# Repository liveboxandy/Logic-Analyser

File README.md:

# Logic-Analyser
Cloned and modified from  (https://github.com/gusmanb/logicanalyzer)

Changes from the above are,

1 - Pico can be mounted on headers. Suggest Samtec BBL or SL style.
2 - Uses 0805 rather than 0402 SMT components so I can see and solder them.
3 - Has keepout area for Pico WiFi.
4 - PCB is slightly larger than the orignal.
5 - No ther changes that I can remember

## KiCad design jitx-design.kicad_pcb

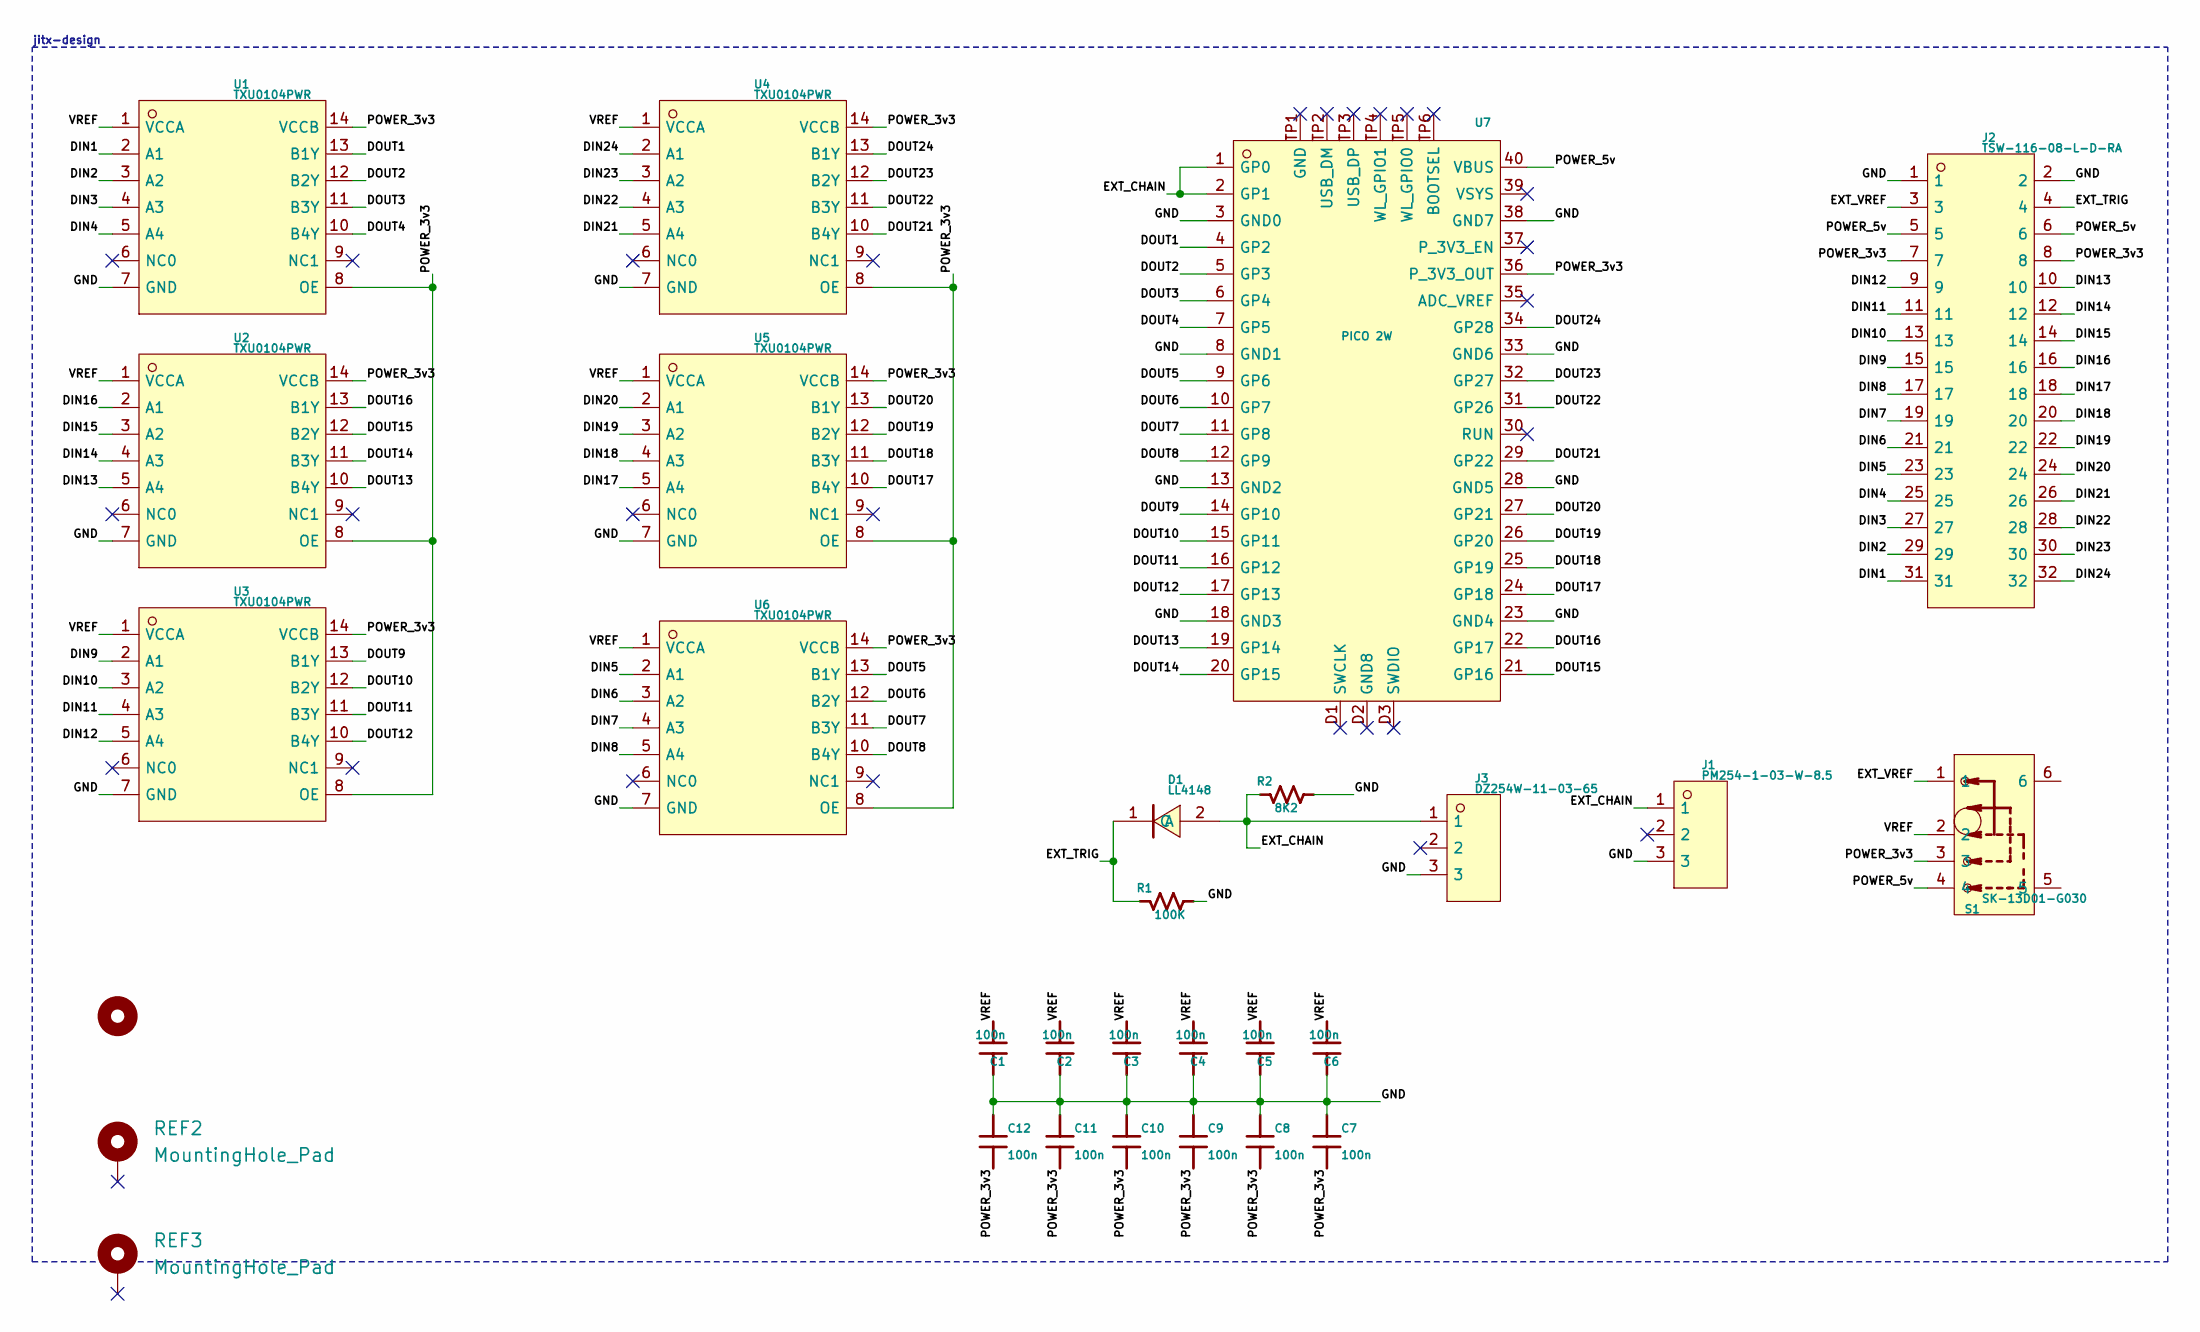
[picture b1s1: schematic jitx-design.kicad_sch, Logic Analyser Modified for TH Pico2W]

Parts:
C1, C2, C3, C4, C5, C6, C7, C8, C9, C10, C11, C12: 100n; C_0805_2012Metric_Pad1.18x1.45mm_HandSolder; MPN 0402X104M160CT
D1: LL4148; LL_34_L3_5_W1_5_RD; MPN LL4148
J1: PM254-1-03-W-8.5; HDR_TH_3P_P2_54_H_F_W10_0_N; MPN PM254-1-03-W-8.5
J2: TSW-116-08-L-D-RA; HDRRA32W64P254_2X16_4064X254X610P
J3: DZ254W-11-03-65; HDR_TH_3P_P2_54_H_M_W10_0; MPN DZ254W-11-03-65
R1: 100K; R_0805_2012Metric_Pad1.20x1.40mm_HandSolder; MPN CRCW0402100KFKEE
R2: 8K2; R_0805_2012Metric_Pad1.20x1.40mm_HandSolder; MPN CR0402AJW-822GLF
REF1: MountingHole_Pad; MountingHole_2.7mm_M2.5_DIN965
REF2, REF3: MountingHole_Pad; MountingHole_2.7mm_M2.5_DIN965_Pad
S1: SK-13D01-G030; SW_TH_SK_13D01_G030; MPN SK-13D01-G030
U1: TXU0104PWR; TSSOP_14_L5_0_W4_4_P0_65_LS6_4_BL_5; MPN TXU0104PWR
U2: TXU0104PWR; TSSOP_14_L5_0_W4_4_P0_65_LS6_4_BL_4; MPN TXU0104PWR
U3: TXU0104PWR; TSSOP_14_L5_0_W4_4_P0_65_LS6_4_BL; MPN TXU0104PWR
U4: TXU0104PWR; TSSOP_14_L5_0_W4_4_P0_65_LS6_4_BL_3; MPN TXU0104PWR
U5: TXU0104PWR; TSSOP_14_L5_0_W4_4_P0_65_LS6_4_BL_1; MPN TXU0104PWR
U6: TXU0104PWR; TSSOP_14_L5_0_W4_4_P0_65_LS6_4_BL_2; MPN TXU0104PWR
U7: PICO 2W; RPi_Pico2W_SMD_TH; MPN PICO

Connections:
/DIN1: J2.31, U1.2 (A1)
/DIN2: J2.29, U1.3 (A2)
/DIN3: J2.27, U1.4 (A3)
/DIN4: J2.25, U1.5 (A4)
/DIN5: J2.23, U6.2 (A1)
/DIN6: J2.21, U6.3 (A2)
/DIN7: J2.19, U6.4 (A3)
/DIN8: J2.17, U6.5 (A4)
/DIN9: J2.15, U3.2 (A1)
/DIN10: J2.13, U3.3 (A2)
/DIN11: J2.11, U3.4 (A3)
/DIN12: J2.9, U3.5 (A4)
/DIN13: J2.10, U2.5 (A4)
/DIN14: J2.12, U2.4 (A3)
/DIN15: J2.14, U2.3 (A2)
/DIN16: J2.16, U2.2 (A1)
/DIN17: J2.18, U5.5 (A4)
/DIN18: J2.20, U5.4 (A3)
/DIN19: J2.22, U5.3 (A2)
/DIN20: J2.24, U5.2 (A1)
/DIN21: J2.26, U4.5 (A4)
/DIN22: J2.28, U4.4 (A3)
/DIN23: J2.30, U4.3 (A2)
/DIN24: J2.32, U4.2 (A1)
/DOUT1: U1.13 (B1Y), U7.4 (GP2)
/DOUT2: U1.12 (B2Y), U7.5 (GP3)
/DOUT3: U1.11 (B3Y), U7.6 (GP4)
/DOUT4: U1.10 (B4Y), U7.7 (GP5)
/DOUT5: U6.13 (B1Y), U7.9 (GP6)
/DOUT6: U6.12 (B2Y), U7.10 (GP7)
/DOUT7: U6.11 (B3Y), U7.11 (GP8)
/DOUT8: U6.10 (B4Y), U7.12 (GP9)
/DOUT9: U3.13 (B1Y), U7.14 (GP10)
/DOUT10: U3.12 (B2Y), U7.15 (GP11)
/DOUT11: U3.11 (B3Y), U7.16 (GP12)
/DOUT12: U3.10 (B4Y), U7.17 (GP13)
/DOUT13: U2.10 (B4Y), U7.19 (GP14)
/DOUT14: U2.11 (B3Y), U7.20 (GP15)
/DOUT15: U2.12 (B2Y), U7.21 (GP16)
/DOUT16: U2.13 (B1Y), U7.22 (GP17)
/DOUT17: U5.10 (B4Y), U7.24 (GP18)
/DOUT18: U5.11 (B3Y), U7.25 (GP19)
/DOUT19: U5.12 (B2Y), U7.26 (GP20)
/DOUT20: U5.13 (B1Y), U7.27 (GP21)
/DOUT21: U4.10 (B4Y), U7.29 (GP22)
/DOUT22: U4.11 (B3Y), U7.31 (GP26)
/DOUT23: U4.12 (B2Y), U7.32 (GP27)
/DOUT24: U4.13 (B1Y), U7.34 (GP28)
/EXT_CHAIN: D1.2 (A), J1.1, J3.1, R2.1, U7.1 (GP0), U7.2 (GP1)
/EXT_TRIG: D1.1 (C), J2.4, R1.1
/EXT_VREF: J2.3, S1.1
/GND: C1.1, C2.1, C3.1, C4.1, C5.1, C6.1, C7.1, C8.1, C9.1, C10.1, C11.1, C12.1, J1.3, J2.1, J2.2, J3.3, R1.2, R2.2, U1.7 (GND), U2.7 (GND), U3.7 (GND), U4.7 (GND), U5.7 (GND), U6.7 (GND), U7.3 (GND0), U7.8 (GND1), U7.13 (GND2), U7.18 (GND3), U7.23 (GND4), U7.28 (GND5), U7.33 (GND6), U7.38 (GND7)
/POWER_3v3: C7.2, C8.2, C9.2, C10.2, C11.2, C12.2, J2.7, J2.8, S1.3, U1.8 (OE), U1.14 (VCCB), U2.8 (OE), U2.14 (VCCB), U3.8 (OE), U3.14 (VCCB), U4.8 (OE), U4.14 (VCCB), U5.8 (OE), U5.14 (VCCB), U6.8 (OE), U6.14 (VCCB), U7.36 (P_3V3_OUT)
/POWER_5v: J2.5, J2.6, S1.4, U7.40 (VBUS)
/VREF: C1.2, C2.2, C3.2, C4.2, C5.2, C6.2, S1.2, U1.1 (VCCA), U2.1 (VCCA), U3.1 (VCCA), U4.1 (VCCA), U5.1 (VCCA), U6.1 (VCCA)

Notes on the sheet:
jitx-design

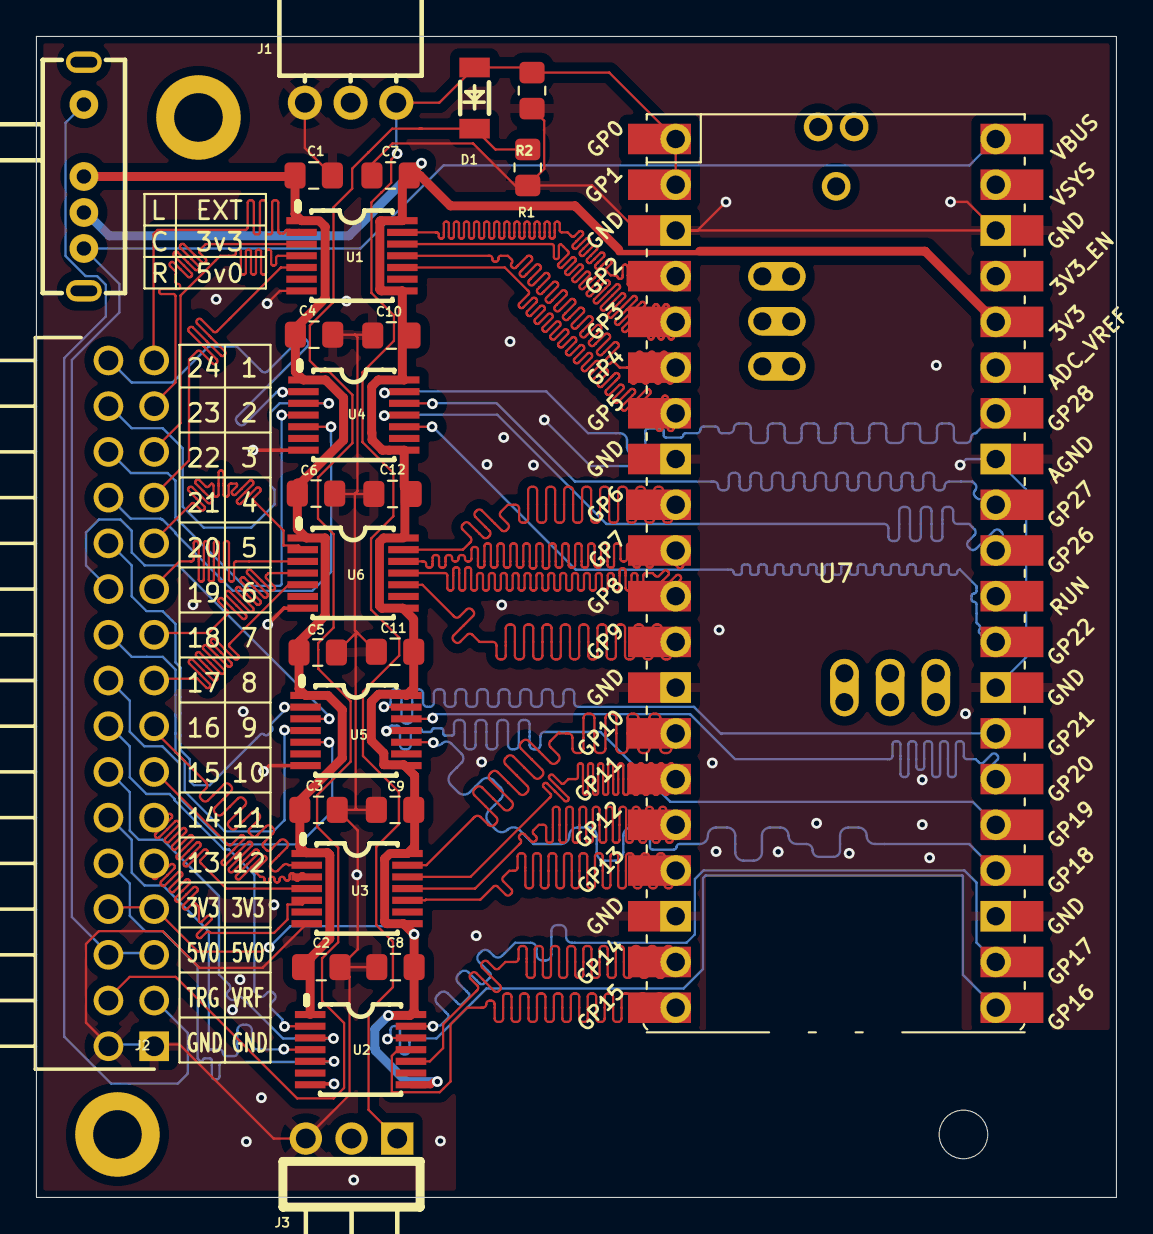
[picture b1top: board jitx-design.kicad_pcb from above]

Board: 2 copper layers, 60.0 x 64.5 mm, 29 parts (0 on the bottom side), 55 nets.

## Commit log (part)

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2026-01-22 Update README with project modifications
    Added modifications and changes to the README.
